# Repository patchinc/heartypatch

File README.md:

ProtoCentral Hearty Patch Single-lead ECG monitor
=======================================================

This repository contains the hardware, firmware and GUI software plans for the HeartyPatch single-lead ECG and R-R interval monitoring device.

## Detailed documentation is available at [heartypatch.protocentral.com](http://heartypatch.protocentral.com/)

For details and updates, check out our Hackaday Page: [https://hackaday.io/project/21046-heartypatch-a-single-lead-ecg-hr-patch-with-esp32](https://hackaday.io/project/21046-heartypatch-a-single-lead-ecg-hr-patch-with-esp32)

You can now buy HeartyPatch at https://www.crowdsupply.com/protocentral/heartypatch

License Information
===================

This product is open source! Both, our hardware and software are open source and licensed under the following licenses:

Hardware
---------

**All hardware is released under [Creative Commons Share-alike 4.0 International](http://creativecommons.org/licenses/by-sa/4.0/).**

You are free to:

* Share — copy and redistribute the material in any medium or format
* Adapt — remix, transform, and build upon the material for any purpose, even commercially.
The licensor cannot revoke these freedoms as long as you follow the license terms.

Under the following terms:

* Attribution — You must give appropriate credit, provide a link to the license, and indicate if changes were made. You may do so in any reasonable manner, but not in any way that suggests the licensor endorses you or your use.
* ShareAlike — If you remix, transform, or build upon the material, you must distribute your contributions under the same license as the original.

Software
--------

**All software is released under the MIT License(http://opensource.org/licenses/MIT).**

THE SOFTWARE IS PROVIDED "AS IS", WITHOUT WARRANTY OF ANY KIND, EXPRESS OR IMPLIED, INCLUDING BUT NOT LIMITED TO THE WARRANTIES OF MERCHANTABILITY, FITNESS FOR A PARTICULAR PURPOSE AND NONINFRINGEMENT. IN NO EVENT SHALL THE AUTHORS OR COPYRIGHT HOLDERS BE LIABLE FOR ANY CLAIM, DAMAGES OR OTHER LIABILITY, WHETHER IN AN ACTION OF CONTRACT, TORT OR OTHERWISE, ARISING FROM, OUT OF OR IN CONNECTION WITH THE SOFTWARE OR THE USE OR OTHER DEALINGS IN THE SOFTWARE.

Please check [*LICENSE.md*](LICENSE.md) for detailed license descriptions.

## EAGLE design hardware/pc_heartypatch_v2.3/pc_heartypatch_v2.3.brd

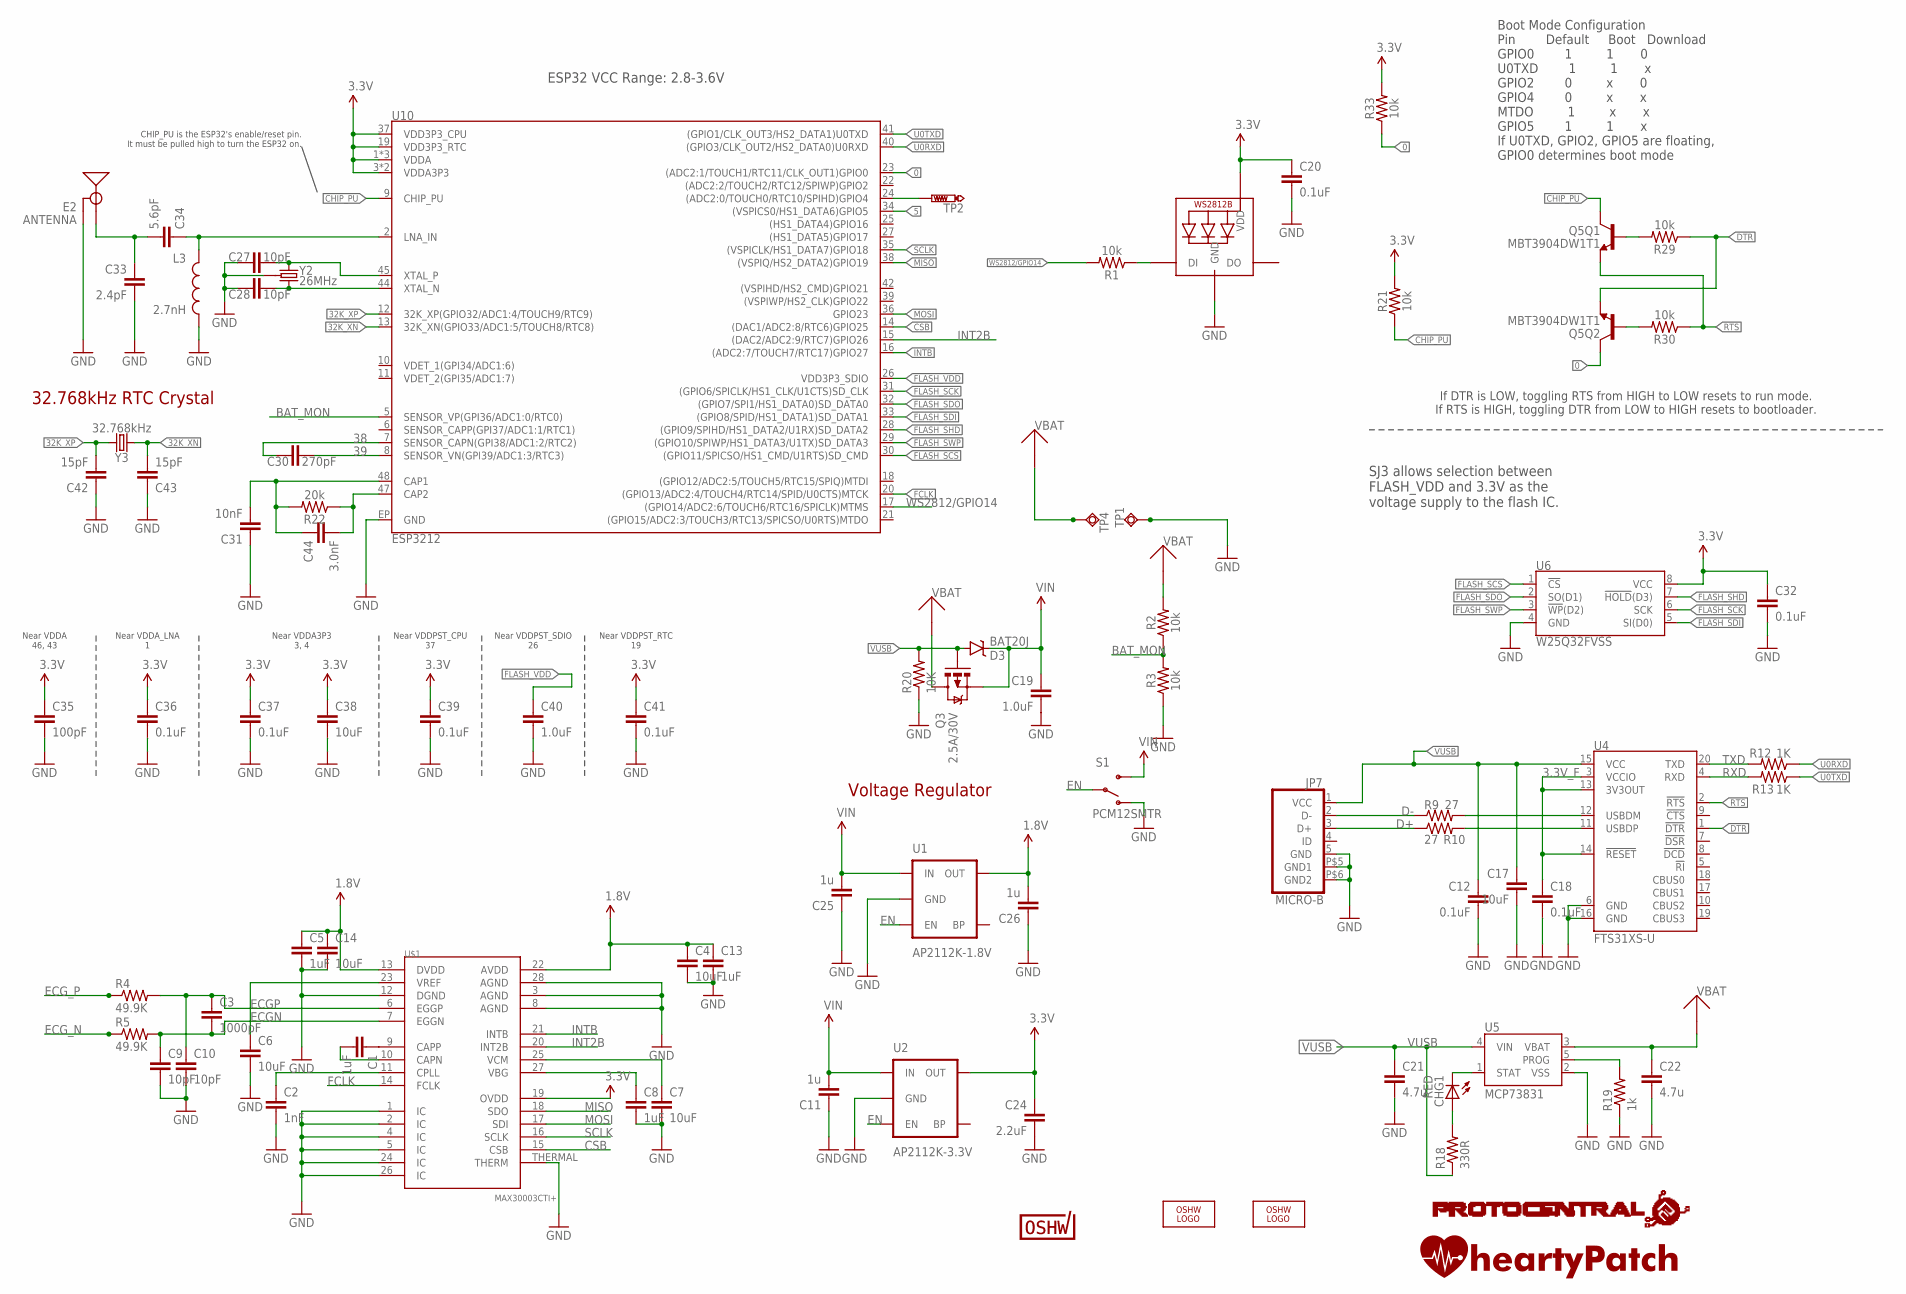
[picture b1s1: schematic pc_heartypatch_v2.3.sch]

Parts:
C1: 1uF; C0603
C2: 1nF; C0603
C3: 1000pF; C0402
C4, C6, C7, C17: 10uF; C0805
C5: 1uF; C0402
C8, C13: 1uF; C0805
C9, C10: 10pF; C0402
C11, C25, C26: 1u; C0402
C12, C18: 0.1uF; C0402
C14: 10uF; C0603
C19: 1.0uF; C0402
C20, C36, C37, C41: 0.1uF; 0603
C21, C22: 4.7u; C0805
C24: 2.2uF; C0402
C27, C28: 10pF; 0603
C30: 270pF; 0603
C31: 10nF; 0603
C32, C39: 0.1uF; 0402
C33: 2.4pF; 0603
C34: 5.6pF; 0603
C35: 100pF; 0603
C38: 10uF; 0603
C40: 1.0uF; 0603
C42, C43: 15pF; 0603
C44: 3.0nF; 0603
CHG1: RED; CHIPLED_0603
D3: BAT20J; SOD-323
E2: ANTENNA; TRACE_ANTENNA_2.4GHZ_25.7MM_TUNED
JP7: MICRO-B
L3: 2.7nH; 0603
LED1: WS2812B5050; WS2812B
LOGO1, LOGO2: OSHW_LOGO_FILLX0200-NT; OSHW_FILLX200_NOTEXT
Q3: 2.5A/30V; SOT23-3
Q5: MBT3904DW1T1; SC70-6
R1, R2, R3, R21, R29, R30, R33: 10k; 0603
R4, R5: 49.9K; 0805
R9, R10: 27; R0402
R12, R13: 1K; R0402
R18: 330R; R0402
R19: 1k; R0402
R20: 10K; R0402
R22: 20k; 0603
S1: PCM12SMTR; SWITCH-SPST-SMD-A
TP1, TP4: TPSQTP20SQ; TP20SQ
TP2: PTR1TP10SQ; TP10SQ
U1: AP2112K-1.8V; SOT23-5
U2: AP2112K-3.3V; SOT23-5
U4: FTS31XS-U; SSOP20_L
U5: MCP73831; SOT23-5
U6: W25Q32FVSS; SOIC-8
U10: ESP3212; QFN48-0.4MM
U$1: MAX30003CTI+; QFN-28
U$8: HEARTYPATCHHEART; HEARTYPATCH
U$9: PROTY_LOGO_WITH_TEXT; PROTY_WITH_TEXT
U$10: CERT-SMALL; CERT-SMALL-SILK
Y2: 26MHz; CRYSTAL-SMD-3.2X2.5
Y3: 32.768kHz; CRYSTAL-SMD-3.2X1.5MM

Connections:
0: Q5.6 (C), R33.1, U10.23 ((ADC2:1/TOUCH1/RTC11/CLK_OUT1)GPIO0)
1.8V: C4.1, C5.1, C13.1, C14.1, C26.2, U1.5 (OUT), U$1.13 (DVDD), U$1.22 (AVDD)
3.3V: C20.1, C24.1, C32.1, C35.1, C36.1, C37.1, C38.1, C39.1, C41.1, LED1.1-VDD (VDD), R21.2, R33.2, U2.5 (OUT), U6.8 (VCC), U10.1 (VDDA), U10.3 (VDDA3P3), U10.4 (VDDA3P3), U10.19 (VDD3P3_RTC), U10.37 (VDD3P3_CPU), U10.43 (VDDA), U10.46 (VDDA), U$1.19 (OVDD)
3.3V_F: C18.1, U4.3 (VCCIO), U4.13 (3V3OUT), U4.14 (!RESET)
5: U10.34 ((VSPICS0/HS1_DATA6)GPIO5)
32K_XN: C43.2, U10.13 (32K_XN(GPIO33/ADC1:5/TOUCH8/RTC8)), Y3.P$2 (2)
32K_XP: C42.2, U10.12 (32K_XP(GPIO32/ADC1:4/TOUCH9/RTC9)), Y3.P$1 (1)
38: C30.1, U10.7 (SENSOR_CAPN(GPI38/ADC1:2/RTC2))
39: C30.2, U10.8 (SENSOR_VN(GPI39/ADC1:3/RTC3))
BAT_MON: R2.1, R3.2, U10.5 (SENSOR_VP(GPI36/ADC1:0/RTC0))
CAP_10N: C31.2, C44.1, R22.2, U10.48 (CAP1)
CHIP_PU: Q5.3 (C), R21.1, U10.9 (CHIP_PU)
CSB: U10.14 ((DAC1/ADC2:8/RTC6)GPIO25), U$1.15 (CSB)
D+: JP7.3 (D+), R10.1
D-: JP7.2 (D-), R9.1
DTR: Q5.1 (E), R29.1, U4.1 (!DTR)
ECGN: C3.2, C9.1, R5.2, U$1.7 (EGGN)
ECGP: C3.1, C10.1, R4.2, U$1.6 (EGGP)
ECG_N: R5.1
ECG_P: R4.1
EN: S1.2, U1.3 (EN), U2.3 (EN)
FCLK: U10.20 ((GPIO13/ADC2:4/TOUCH4/RTC14/SPID/U0CTS)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), U$1.14 (FCLK)
FLASH_SCK: U6.6 (SCK), U10.31 ((GPIO6/SPICLK/HS1_CLK/U1CTS)SD_CLK)
FLASH_SCS: U6.1 (!CS!), U10.30 ((GPIO11/SPICSO/HS1_CMD/U1RTS)SD_CMD)
FLASH_SDI: U6.5 (SI(D0)), U10.33 ((GPIO8/SPID/HS1_DATA1)SD_DATA1)
FLASH_SDO: U6.2 (SO(D1)), U10.32 ((GPIO7/SPI1/HS1_DATA0)SD_DATA0)
FLASH_SHD: U6.7 (!HOLD!(D3)), U10.28 ((GPIO9/SPIHD/HS1_DATA2/U1RX)SD_DATA2)
FLASH_SWP: U6.3 (!WP!(D2)), U10.29 ((GPIO10/SPIWP/HS1_DATA3/U1TX)SD_DATA3)
FLASH_VDD: C40.1, U10.26 (VDD3P3_SDIO)
GND: C2.2, C4.2, C5.2, C6.2, C7.2, C8.2, C9.2, C10.2, C11.1, C12.2, C13.2, C14.2, C17.2, C18.2, C19.2, C20.2, C21.2, C22.2, C24.2, C25.1, C26.1, C27.1, C28.1, C31.1, C32.2, C33.2, C35.2, C36.2, C37.2, C38.2, C39.2, C40.2, C41.2, C42.1, C43.1, E2.GND, E2.GND2 (GND), JP7.5 (GND), JP7.P$5 (GND1), JP7.P$6 (GND2), L3.2, LED1.3-GND (GND), R3.1, R19.1, R20.1, S1.1 (O), TP1.TP, U1.2 (GND), U2.2 (GND), U4.6 (GND), U4.16 (GND), U5.2 (VSS), U6.4 (GND), U10.EP (GND), U$1.1 (IC), U$1.2 (IC), U$1.3 (AGND), U$1.4 (IC), U$1.5 (IC), U$1.8 (AGND), U$1.12 (DGND), U$1.24 (IC), U$1.26 (IC), U$1.28 (AGND), U$1.THERMAL (THERM), Y2.2 (GND), Y2.4 (GND)
INT2B: U10.15 ((DAC2/ADC2:9/RTC7)GPIO26), U$1.20 (INT2B)
INTB: U10.16 ((ADC2:7/TOUCH7/RTC17)GPIO27), U$1.21 (INTB)
LNA_IN: C34.1, L3.1, U10.2 (LNA_IN)
MISO: U10.38 ((VSPIQ/HS2_DATA2)GPIO19), U$1.18 (SDO)
MOSI: U10.36 (GPIO23), U$1.17 (SDI)
unnamed: LED1.4-DIN (DI), R1.1
unnamed: C6.1, U$1.23 (VREF)
unnamed: C1.1, U$1.9 (CAPP)
unnamed: TP2.TP, U10.24 ((ADC2:0/TOUCH0/RTC10/SPIHD)GPIO4)
unnamed: CHG1.C, U5.1 (STAT)
unnamed: C1.2, U$1.10 (CAPN)
unnamed: C2.1, U$1.11 (CPLL)
unnamed: R9.2, U4.12 (USBDM)
unnamed: R10.2, U4.11 (USBDP)
unnamed: C7.1, U$1.25 (VCM)
unnamed: C8.1, U$1.27 (VBG)
unnamed: CHG1.A, R18.2
unnamed: R19.2, U5.5 (PROG)
unnamed: Q5.5 (B), R29.2
unnamed: Q5.2 (B), R30.2
unnamed: C27.2, U10.45 (XTAL_P), Y2.1
unnamed: C28.2, U10.44 (XTAL_N), Y2.3 (2)
unnamed: C44.2, R22.1, U10.47 (CAP2)
RTS: Q5.4 (E), R30.1, U4.2 (!RTS)
RXD: R13.2, U4.4 (RXD)
SCLK: U10.35 ((VSPICLK/HS1_DATA7)GPIO18), U$1.16 (SCLK)
TRACE_ANT1: C33.1, C34.2, E2.ANT (SIGNAL)
TXD: R12.2, U4.20 (TXD)
U0RXD: R12.1, U10.40 ((GPIO3/CLK_OUT2/HS2_DATA0)U0RXD)
U0TXD: R13.1, U10.41 ((GPIO1/CLK_OUT3/HS2_DATA1)U0TXD)
VBAT: C22.1, Q3.3 (D), R2.2, TP4.TP, U5.3 (VBAT)
VIN: C11.2, C19.1, C25.2, D3.C, Q3.2 (S), S1.3 (S), U1.1 (IN), U2.1 (IN)
VUSB: C12.1, C17.1, C21.1, D3.A, JP7.1 (VCC), Q3.1 (G), R18.1, R20.2, U4.15 (VCC), U5.4 (VIN)
WS2812/GPIO14: R1.2, U10.17 ((GPIO14/ADC2:6/TOUCH6/RTC16/SPICLK)MTMS)

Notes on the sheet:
Boot Mode Configuration Pin Default Boot Download GPIO0 1 1 0 U0TXD 1 1 x GPIO2 0 x 0 GPIO4 0 x x MTDO 1 x x GPIO5 1 1 x If U0TXD, GPIO2, GPIO5 are floating, GPIO0 determines boot mode
Near VDDA 46, 43
Near VDDA_LNA 1
Near VDDA3P3 3, 4
Near VDDPST_CPU 37
Near VDDPST_SDIO 26
Near VDDPST_RTC 19
32.768kHz RTC Crystal
ESP32 VCC Range: 2.8-3.6V
SJ3 allows selection between FLASH_VDD and 3.3V as the voltage supply to the flash IC.
If DTR is LOW, toggling RTS from HIGH to LOW resets to run mode. If RTS is HIGH, toggling DTR from LOW to HIGH resets to bootloader.
CHIP_PU is the ESP32's enable/reset pin. It must be pulled high to turn the ESP32 on.
Voltage Regulator

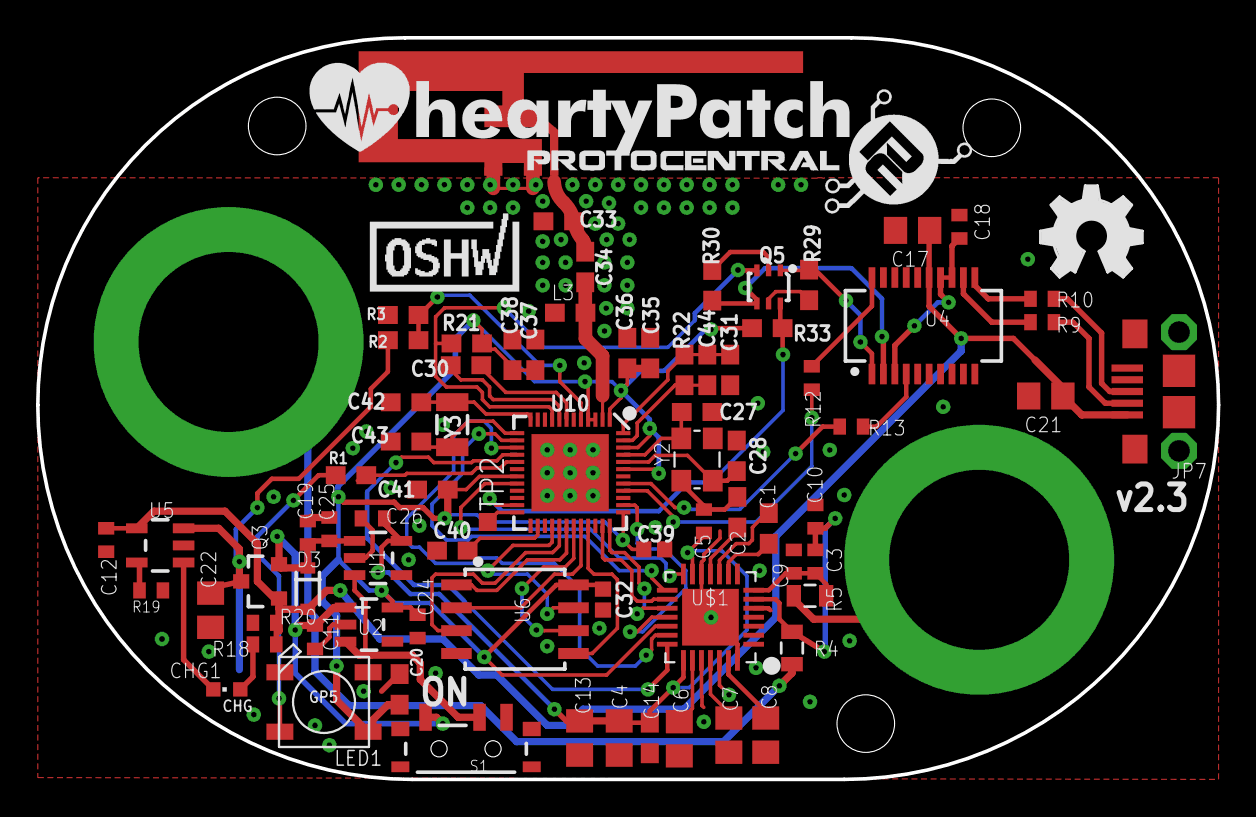
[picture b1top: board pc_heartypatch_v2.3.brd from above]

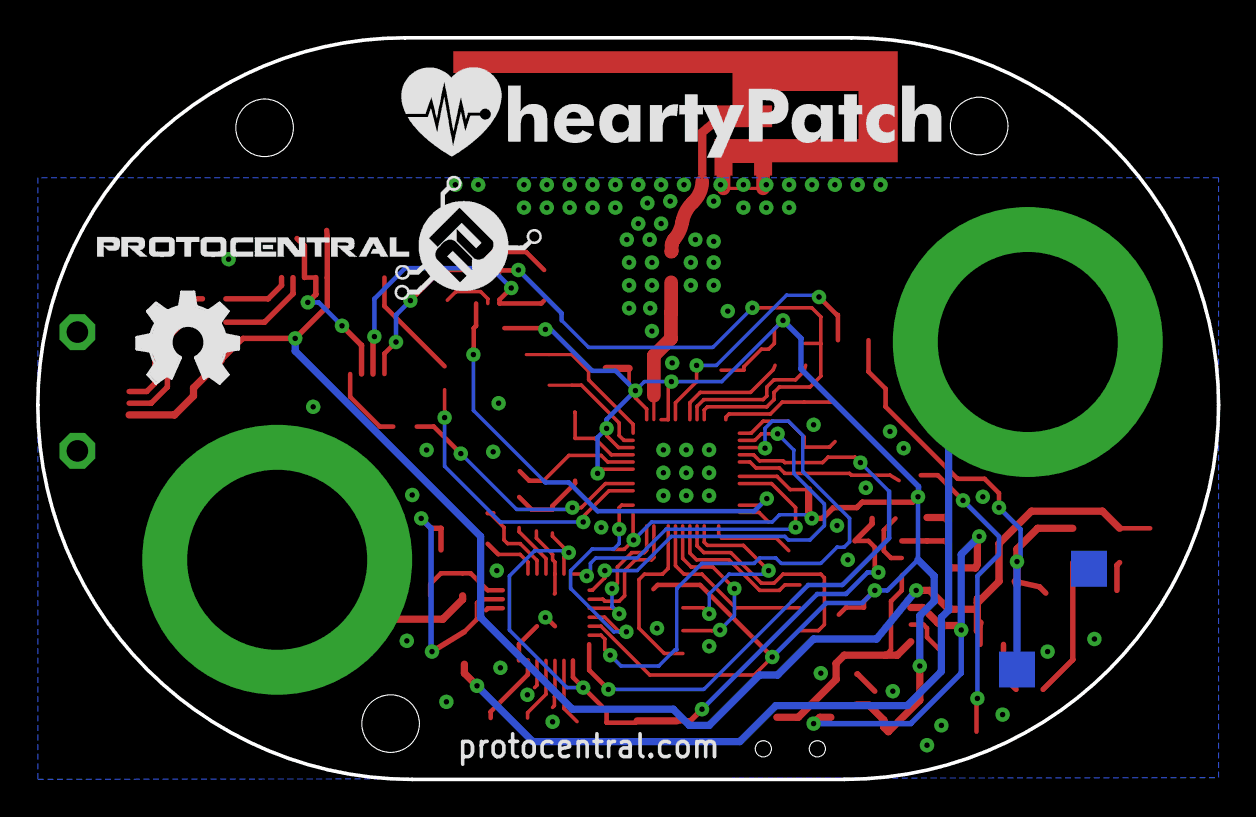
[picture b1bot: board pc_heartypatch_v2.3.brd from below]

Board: 4 copper layers, 65.6 x 41.2 mm, 85 parts (5 on the bottom side), 61 nets.

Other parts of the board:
U$4: HEARTYPATCHHEART; HEARTYPATCH
U$7: PROTY_LOGO_WITH_TEXT; PROTY_WITH_TEXT

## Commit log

2017-05-04 Init new repository
2017-05-05 [added ble]
2017-05-05 ble code
2017-05-08 Edited Readme
2017-06-12 Updated firmware for AWS IoT
2017-07-22 Added new firmware for Hearty
    1. Interrupt Driven Code
    2. Support for BLE
2017-07-22 Added HeartyPatch enclosure files
2017-08-20 Added new v3 board and schematic
2017-09-30 Updated and organised all Firmware/GUI
2017-11-16 Added Android app APK only
2017-12-16 Create CNAME
2017-12-16 Set theme jekyll-theme-minimal
2017-12-16 Added docs
2017-12-16 Updated docs for HeartyPatch
2017-12-30 Updated HeartyPatch docs
2017-12-30 Added video to Quickstart docs
2017-12-30 Update docs, again
2018-01-08 Modified docs config
2018-01-08 Updated docs
2018-01-15 Added latest HeartyPatch BLE code
2018-01-15 Removed pc_heartypatch code
2018-01-15 Remove README
2018-01-16 Added TCP streaming firmware
2018-01-16 Minor corrections in docs
2018-01-16 More minor changes to docs
2018-01-16 Checking
2018-01-16 Trying out docs theme
2018-01-16 Minor changes to docs theme
2018-01-16 config.yml changes
2018-01-16 Added _pages folder
2018-01-17 edited the documentation
2018-01-17 edited the documentation file
2018-01-17 Modified TCP streaming GUI code
2018-01-19 Add docs for streaming mode
2018-01-19 Removed GUI for HRV, will add later
2018-01-19 Added stuff to streaming ecg mode docs
2018-01-27 Updated esp-idf and espressif toolchain versions in docs
2018-02-01 Updated docs to include versions of esp-idf
2018-02-01 Updated docs firmware upgrades
2018-02-26 Bugfix update for TCP server firmware and GUI software
2018-03-02 Added HeartyPatch v2.3 schematics
2018-03-09 Fix sample rate consistency issue
    ALso make sample rate of DHPF configurable at from menuconfig
2018-03-10 Added HRV functionality to TCP GUI
2018-03-11 Add Stats and Protocol Constants
2018-03-11 Modularize Register Reads
2018-03-11 Configurable samples per packet
    Still limitted to legacy packet size
2018-03-12 packetsize bug fix
2018-03-12 cleanup pointer management
2018-03-12 Stats reporting controlled from config menu
2018-03-12 Clear ECG FIFO and counters at start of each new connection
2018-03-12 add comments
2018-03-12 Updated docs for firmware upgrades
2018-03-12 Minor changes to docs
2018-03-12 cosmetic changes
2018-03-13 Updater GUI and add Downloader
    GUI updated for V3 protocol
2018-03-13 Update headers
    Also format output for log file
2018-03-14 Quiesce send_data between connections
    Optimize power by putting Max30003 in default state between connections
2018-03-15 Final compiling code, building well
2018-03-15 Updated docs with new packet format
2018-03-15 Added new faq section to docs
2018-03-15 Updated FAQ
2018-03-15 Bug Fix - kill send_data task
    Kill send_data task more gracefully to avoid ESP32 crash/restart
2018-03-15 optimize restart time
2018-03-16 Quiesce bug fix
2018-03-16 Updated theme for docs
2018-03-16 Updated theme settings
2018-03-16 Update docs image sizes
2018-03-16 Update docs
2018-03-16 Updated the doc images
2018-03-16 Updated docs again
2018-03-16 Adds supports for interrupts
    Also reduced stats message since larger amounts of text was limiting realtime performance resulting in FIFO overflows
2018-03-16 Added new Python script, updated docs
2018-03-16 Updated FAQ section of docs
2018-03-16 Corrected FAQ section
2018-03-16 Corrections
2018-03-16 Minor corrections
2018-03-16 Docs: corrected some links
2018-04-17 minor edits, sdnn
2018-07-19 Added support for esp-idf 3.1, HRV badge design
2018-08-18 Updated HRV DEFCON badge code
2018-09-08 Update CNAME
2018-11-23 Added arrhythmia detection feature
2019-06-25 Added update firmware documentation
2019-06-25 Update image sizes
2024-12-11 updated docs/jekyll-docs-theme.gemspec

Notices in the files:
README.md:
CC-BY-SA-4.0
parts and their libraries:
SparkFun-Capacitors: Licensing: Creative Commons ShareAlike 4.0 International - https://creativecommons.org/licenses/by-sa/4.0
SparkFun-DigitalIC: Licensing: CC v3.0 Share-Alike You are welcome to use this library for commercial purposes.
